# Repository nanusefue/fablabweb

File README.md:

## FAB ACADEMY 2017

This is the repository that contains all the work done at the Fab Academy of 2017 at FabLab Barcelona:

> [Archive FabAcademy 2017](http://archive.fabacademy.org/archives/2017/fablabbcn/students/271/)

> [Git Page FabAcademy 2017](https://nanusefue.github.io/fablabweb/)

#### Esteban Martin Gimenez

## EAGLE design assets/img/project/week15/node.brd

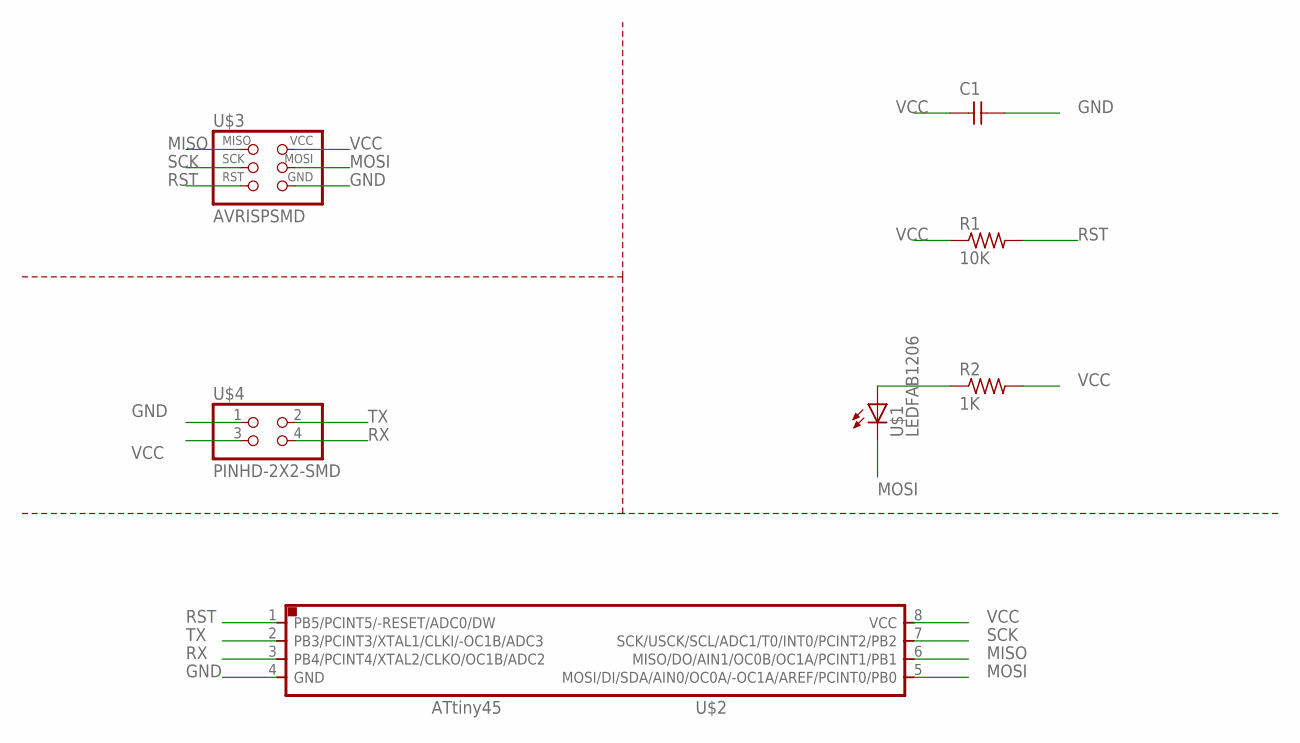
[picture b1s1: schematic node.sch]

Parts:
C1: CAP-UNPOLARIZED; C1206
R1: 10K; R1206FAB
R2: 1K; R1206FAB
U$1: LEDFAB1206; LED1206FAB
U$2: ATTINY45SI; SOIC8
U$3: AVRISPSMD; 2X03SMD
U$4: PINHD-2X2-SMD; 2X02SMD

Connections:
GND: C1.2, U$2.4 (GND), U$3.6 (GND), U$4.1
MISO: U$2.6 (MISO/DO/AIN1/OC0B/OC1A/PCINT1/PB1), U$3.1 (MISO)
MOSI: U$1.2 (C), U$2.5 (MOSI/DI/SDA/AIN0/OC0A/-OC1A/AREF/PCINT0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), U$3.4 (MOSI)
unnamed: R2.1, U$1.1 (A)
RST: R1.2, U$2.1 (PB5/PCINT5/-RESET/ADC0/DW), U$3.5 (RST)
RX: U$2.3 (PB4/PCINT4/XTAL2/CLKO/OC1B/ADC2), U$4.4
SCK: U$2.7 (SCK/USCK/SCL/ADC1/T0/INT0/PCINT2/PB2), U$3.3 (SCK)
TX: U$2.2 (PB3/PCINT3/XTAL1/CLKI/-OC1B/ADC3), U$4.2
VCC: C1.1, R1.1, R2.2, U$2.8 (VCC), U$3.2 (VCC), U$4.3

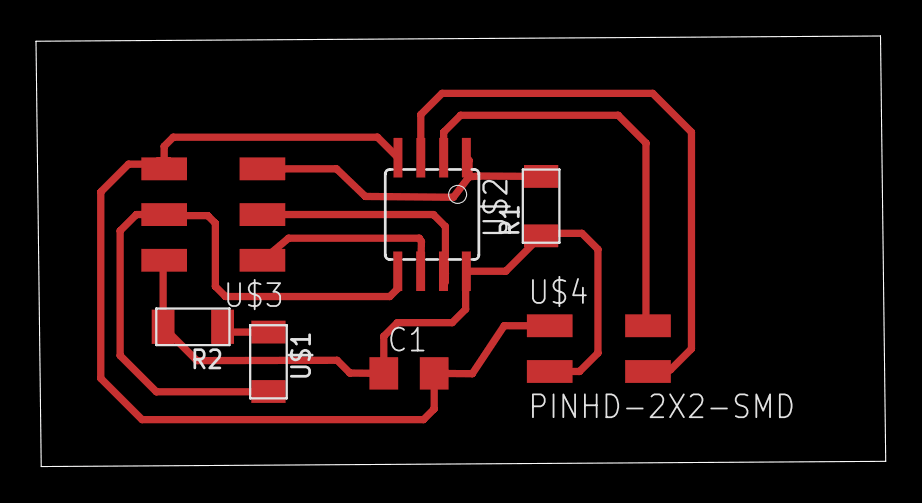
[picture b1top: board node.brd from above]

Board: 2 copper layers, 47.2 x 23.9 mm, 7 parts (0 on the bottom side), 9 nets.

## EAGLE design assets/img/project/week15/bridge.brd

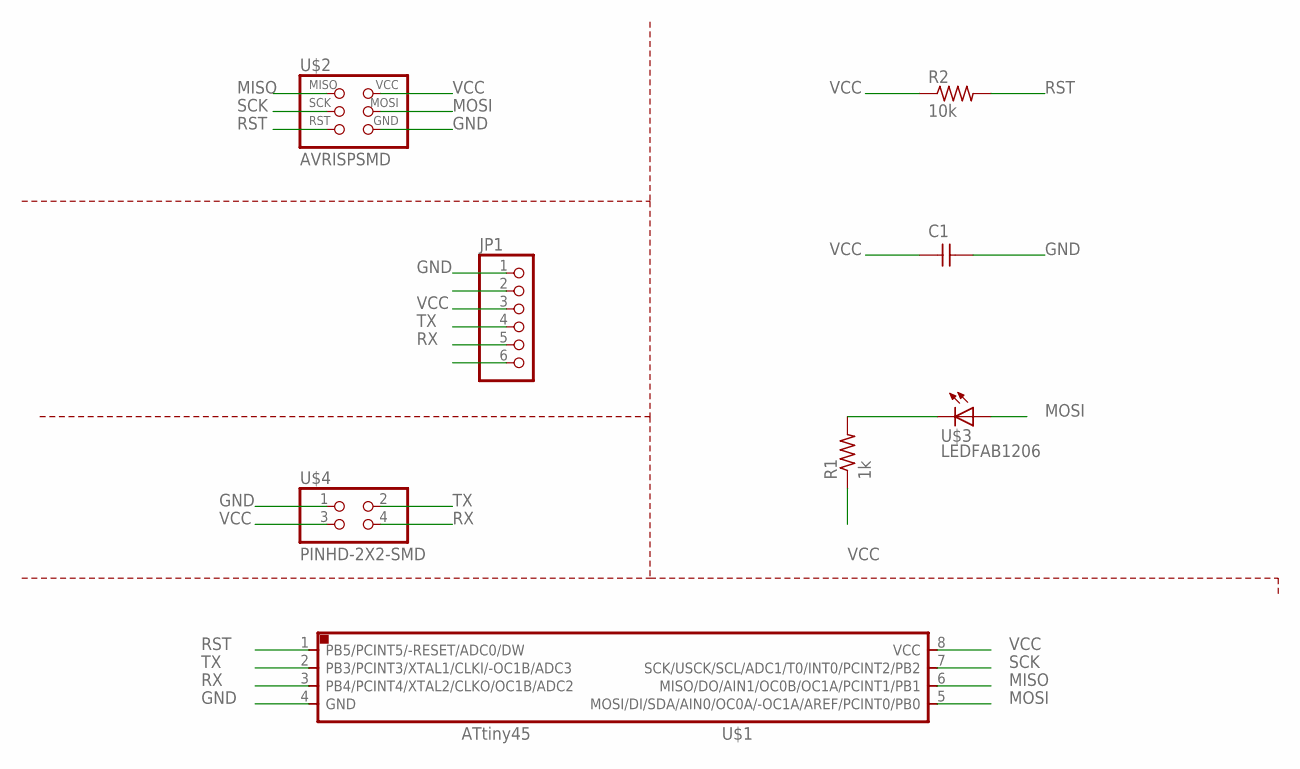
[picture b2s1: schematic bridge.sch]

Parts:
C1: CAP-UNPOLARIZEDFAB; C1206FAB
JP1: PINHD-1X6; 1X06
R1: 1k; R1206FAB
R2: 10k; R1206FAB
U$1: ATTINY45SI; SOIC8
U$2: AVRISPSMD; 2X03SMD
U$3: LEDFAB1206; LED1206FAB
U$4: PINHD-2X2-SMD; 2X02SMD

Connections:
GND: C1.2, JP1.1, U$1.4 (GND), U$2.6 (GND), U$4.1
MISO: U$1.6 (MISO/DO/AIN1/OC0B/OC1A/PCINT1/PB1), U$2.1 (MISO)
MOSI: U$1.5 (MOSI/DI/SDA/AIN0/OC0A/-OC1A/AREF/PCINT0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), U$2.4 (MOSI), U$3.1 (A)
unnamed: R1.2, U$3.2 (C)
RST: R2.2, U$1.1 (PB5/PCINT5/-RESET/ADC0/DW), U$2.5 (RST)
RX: JP1.5, U$1.3 (PB4/PCINT4/XTAL2/CLKO/OC1B/ADC2), U$4.4
SCK: U$1.7 (SCK/USCK/SCL/ADC1/T0/INT0/PCINT2/PB2), U$2.3 (SCK)
TX: JP1.4, U$1.2 (PB3/PCINT3/XTAL1/CLKI/-OC1B/ADC3), U$4.2
VCC: C1.1, JP1.3, R1.1, R2.1, U$1.8 (VCC), U$2.2 (VCC), U$4.3

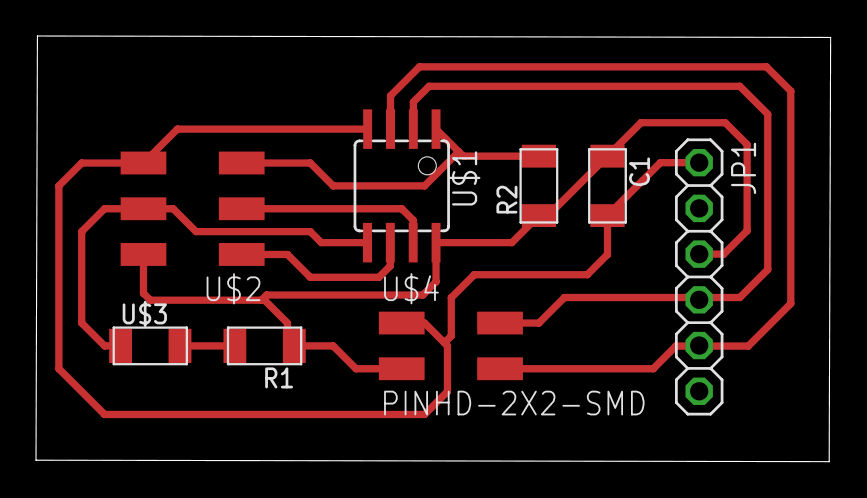
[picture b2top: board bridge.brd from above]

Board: 2 copper layers, 44.1 x 23.6 mm, 8 parts (0 on the bottom side), 9 nets.

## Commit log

2017-02-01 fist commit
2017-02-01 fix url
2017-02-01 git image
2017-02-01 delete
2017-02-01 change img size
2017-02-01 new images
2017-02-01 update jekyll
2017-02-05 se agrego la opcion de una draft y se extendio la doc de la primer semana
2017-05-01 se añadio nuevas semana
2017-05-01 assignamet nuevo
2017-05-01 add new images
2017-05-03 code adxl
2017-05-03 chip
2017-05-03 add code arduino
2017-05-21 add image
2017-05-28 add img
2017-05-28 udpdate imag
2017-06-07 add new img
2017-06-07 new img
2017-06-07 vinyl img
2017-06-15 add presentation
2017-06-25 new assignaments
2017-08-07 se agregan nuevos fcheros
2017-10-06 obj stl week3
2017-10-06 3d scan add
2017-10-09 re writte assignaments
2017-10-09 add more text
2017-10-13 assig 5 3 printer
2017-10-15 nuevos assignaments actualizados
2017-10-15 mas assignaments
2017-10-18 update electronics
2017-10-23 update week12
2017-10-23 update img week16
2017-10-24 update week 15
2017-10-24 update week15
2017-10-26 week17
2017-10-26 update week
2017-10-28 update weeks
2017-10-28 update week 19
2017-10-29 file static
2017-10-29 coomit
2017-10-30 updat
2017-11-12 upload
2017-11-12 udpate
2017-12-04 Create CNAME
